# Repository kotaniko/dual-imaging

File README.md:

# Dual-Imaging Display
This prototype is developed in partial fulfillment for a Master's degree to prove that fiber-optic interconnection is a suitable high-speed interconnection for CubeSat platforms. The thesis is available [here](https://gatech.edu).

## Introduction
This repository contains the development details of dual-imaging display using the BF4M fiber-optic module with FPGAs and Raspberry Pi Compute Module 4. The goal of this prototype is to demonstrate the high-speed interconnection using a fiber-optic transceiver for CubeSat platforms.

## Hardware
* Artix-7 FPGA module from Trenz Electronic: [TE0714-03-50-2IAC6](https://shop.trenz-electronic.de/en/TE0714-03-50-2IAC6-FPGA-Module-with-Xilinx-Artix-7-XC7A50T-2CSG325I-1.8V-Configuration-4-x-3-cm)

* [Raspberry Pi Compute Module 4](https://www.raspberrypi.com/products/compute-module-4)

* [BF4M](https://www.hirose.com/product/series/BF4M) fiber-optic module from Hirose Electronic

* [Pcam 5C](https://digilent.com/shop/pcam-5c-5-mp-fixed-focus-color-camera-module) camera module from Digilent

## System Architecture
Below shows the overview of the dual-imaging display system.

MIPI CSI-2 Rx Subsystem IP core is used for interfacing with the camera modules, and Aurora8B10B Ip core for interfacing with the fiber-optic transceiver operating up to 6.25 Gbps. On the receiver FPGA, DMA/Bridge Subsystem for PCI Express IP core is used for interfacing with the Raspberry Pi Compute Module 4 over PCIe.

Post-synthesis re-routing on the RX FPGA is needed for GTP clock signals as Aurora8B10B and PCIe core require different clock source. The details are explained in **Vivado/README.md**.

## Images of the Prototype

## Demonstration Video
Below video demonstrates that the two camera data stream are transmitted to the Raspberry Pi Compute Module 4 at 1.0 Gbps. The RPiCM4 was capable of receiving the data stream to /dev/null at 2.0 Gbps, but the maximum data rate to write the data stream to its RAM was 1.0 Gbps.

https://user-images.githubusercontent.com/22487346/164984304-3e48e70a-c83b-4c12-9497-3e3b185fa539.mov

The validation method discussed in the thesis demonstrated that the BF4M fiber-optic module achieved the maximum data rate of 6.25 Gbps at the power consumption of 90 mW.

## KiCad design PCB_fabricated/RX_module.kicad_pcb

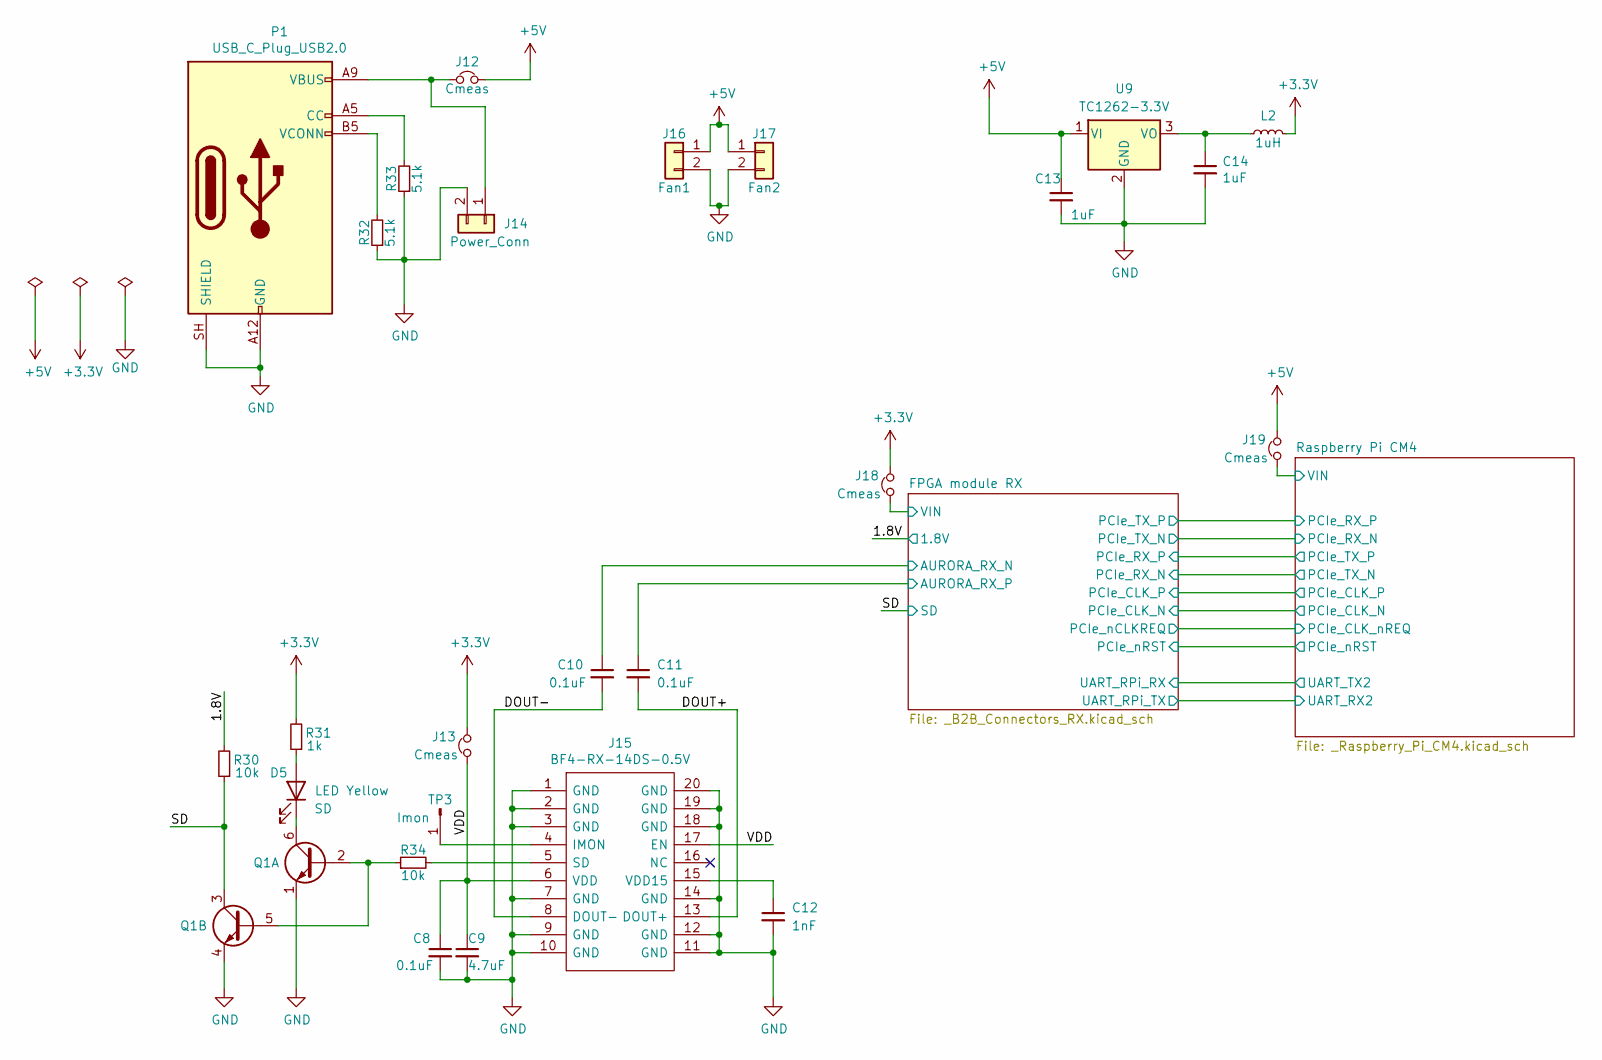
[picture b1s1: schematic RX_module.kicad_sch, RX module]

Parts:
C8, C10, C11: 0.1uF; C_0603_1608Metric_Pad1.08x0.95mm_HandSolder
C9: 4.7uF; C_0603_1608Metric_Pad1.08x0.95mm_HandSolder
C12: 1nF; C_0603_1608Metric_Pad1.08x0.95mm_HandSolder
C13, C14: 1uF; C_0603_1608Metric_Pad1.08x0.95mm_HandSolder
D5: LED Yellow; LED_0603_1608Metric_Pad1.05x0.95mm_HandSolder
J12, J13, J18, J19: Cmeas; PinHeader_1x02_P2.54mm_Vertical
J14: Power_Conn; JST_XH_B2B-XH-A_1x02_P2.50mm_Vertical
J15: BF4-RX-14DS-0.5V; BF4RX14DS05V
J16: Fan1; PinHeader_1x02_P2.54mm_Vertical
J17: Fan2; PinHeader_1x02_P2.54mm_Vertical
L2: 1uH; L_0603_1608Metric_Pad1.05x0.95mm_HandSolder
P1: USB_C_Plug_USB2.0; USB4125-GF-A
Q1: BC847BS; SOT-363_SC-70-6_Handsoldering
R30, R34: 10k; R_0603_1608Metric_Pad0.98x0.95mm_HandSolder
R31: 1k; R_0603_1608Metric_Pad0.98x0.95mm_HandSolder
R32, R33: 5.1k; R_0603_1608Metric_Pad0.98x0.95mm_HandSolder
TP3: Imon; TestPoint_Loop_D2.50mm_Drill1.0mm
U9: TC1262-3.3V; SOT-223-3_TabPin2

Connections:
+3V3: J13.2, J18.2, L2.2, R31.2
+5V: C13.1, J12.2, J16.1, J17.1, J19.2, U9.1 (VI)
/1.8V: R30.2; also elsewhere on the board
/DOUT+: C11.2, J15.13 (DOUT+)
/DOUT-: C10.2, J15.8 (DOUT-)
/FPGA module RX/AURORA_RX_N: C10.1; also elsewhere on the board
/FPGA module RX/AURORA_RX_P: C11.1; also elsewhere on the board
/FPGA module RX/VIN: J18.1; also elsewhere on the board
/Raspberry Pi CM4/VIN: J19.1; also elsewhere on the board
/SD: Q1.3 (C2), R30.1; also elsewhere on the board
/VDD: C8.1, C9.1, J13.1, J15.6 (VDD), J15.17 (EN)
GND: C8.2, C9.2, C12.2, C13.2, C14.2, J14.2, J15.1 (GND), J15.2 (GND), J15.3 (GND), J15.7 (GND), J15.9 (GND), J15.10 (GND), J15.11 (GND), J15.12 (GND), J15.14 (GND), J15.18 (GND), J15.19 (GND), J15.20 (GND), J16.2, J17.2, P1.A12 (GND), P1.B12 (GND), P1.SH (SHIELD), Q1.1 (E1), Q1.4 (E2), R32.1, R33.1, U9.2 (GND); also elsewhere on the board
unnamed: C12.1, J15.15 (VDD15)
unnamed: C14.1, L2.1, U9.3 (VO)
unnamed: D5.1 (K), Q1.6 (C1)
unnamed: D5.2 (A), R31.1
unnamed: J12.1, J14.1, P1.A9 (VBUS)
unnamed: J15.4 (IMON), TP3.1
unnamed: J15.5 (SD), R34.2
unnamed: P1.A5 (CC), R33.2
unnamed: P1.B5 (VCONN), R32.2
unnamed: Q1.2 (B1), Q1.5 (B2), R34.1

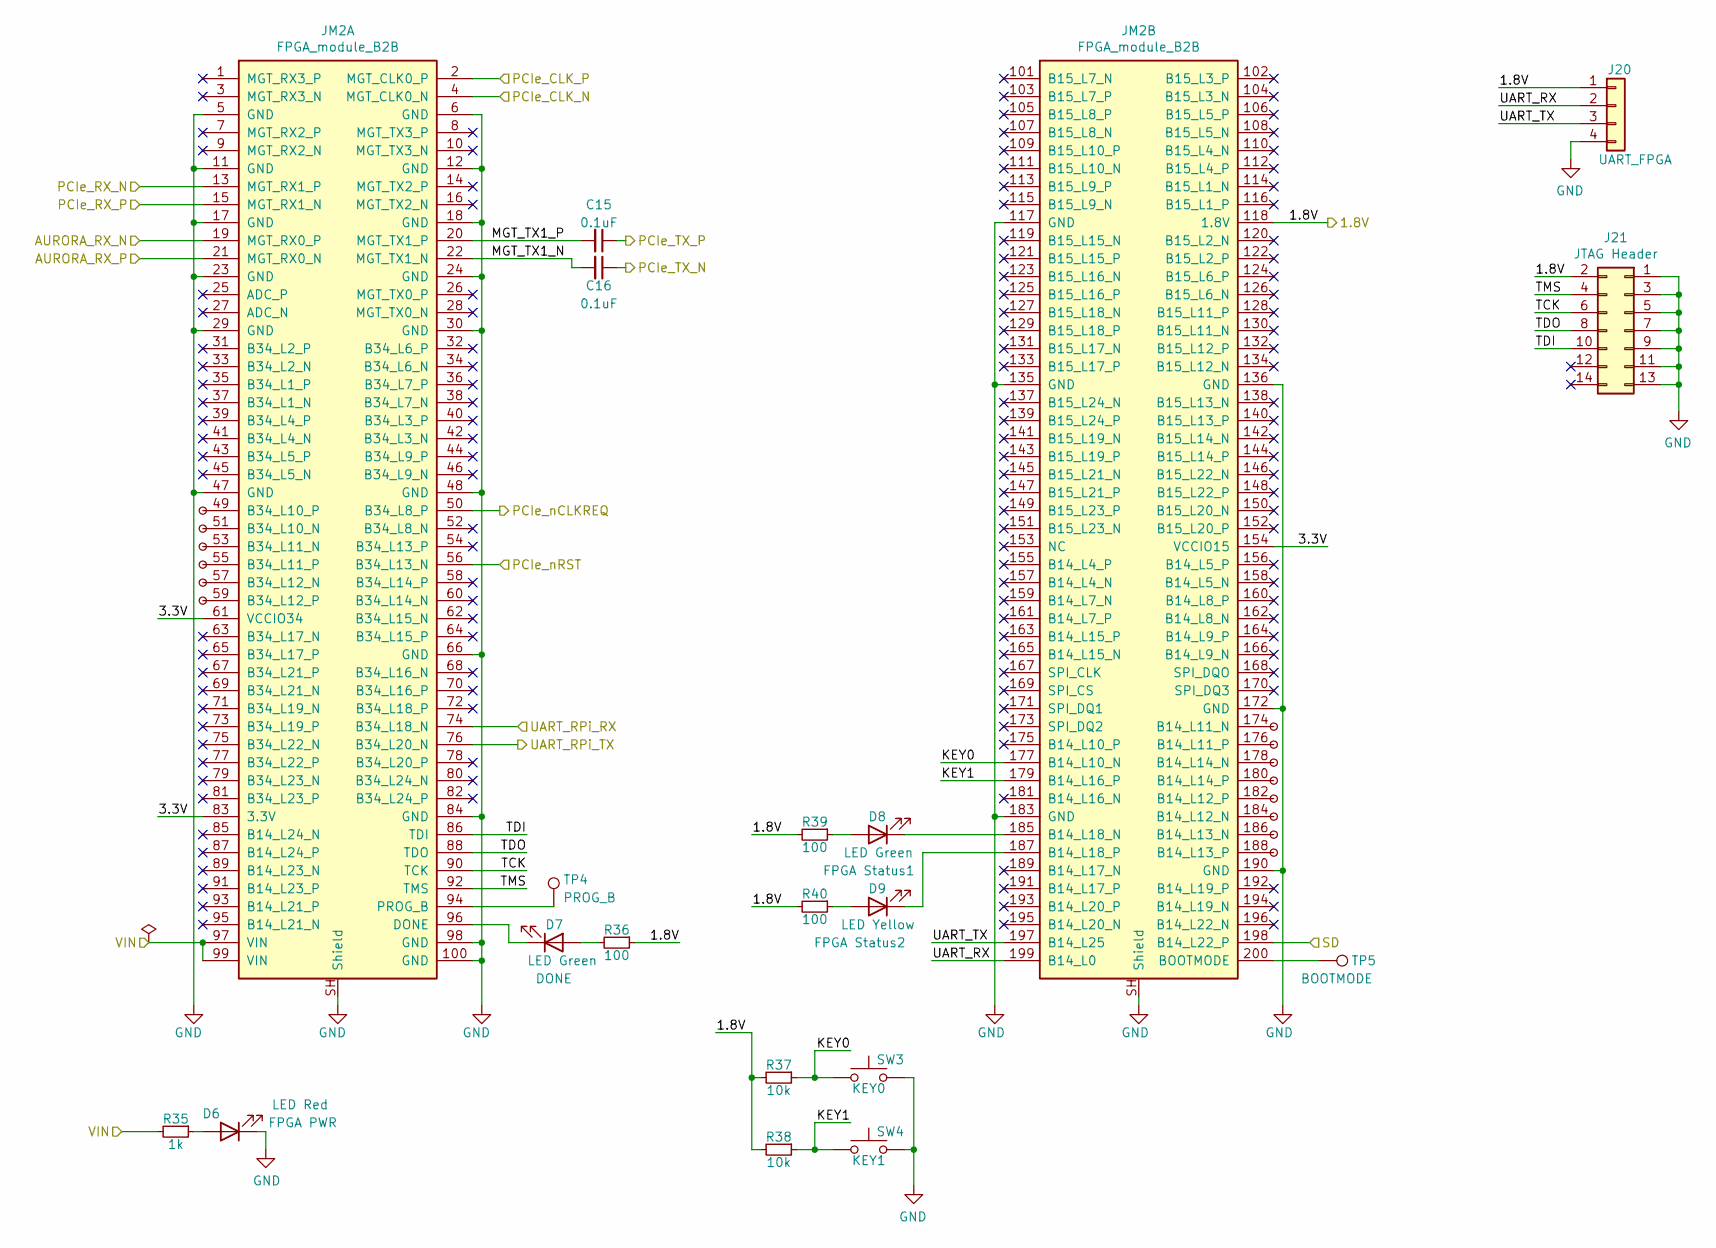
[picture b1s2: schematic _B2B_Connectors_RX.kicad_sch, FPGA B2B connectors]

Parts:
C15, C16: 0.1uF; C_0603_1608Metric_Pad1.08x0.95mm_HandSolder
D6: LED Red; LED_0603_1608Metric_Pad1.05x0.95mm_HandSolder
D7, D8: LED Green; LED_0603_1608Metric_Pad1.05x0.95mm_HandSolder
D9: LED Yellow; LED_0603_1608Metric_Pad1.05x0.95mm_HandSolder
J20: UART_FPGA; PinHeader_1x04_P2.54mm_Vertical
J21: JTAG Header; JTAG_Header
JM2: FPGA_module_B2B
P2, P3, P4, P5, P6, P7, P8, P9, P10, P11, P12, P13, P14, P15: ExtPad; ExtPoint_Pad_1.0x2.0mm
R35: 1k; R_0603_1608Metric_Pad0.98x0.95mm_HandSolder
R36, R39, R40: 100; R_0603_1608Metric_Pad0.98x0.95mm_HandSolder
R37, R38: 10k; R_0603_1608Metric_Pad0.98x0.95mm_HandSolder
SW3: KEY0; SW_SPST_PTS636
SW4: KEY1; SW_SPST_PTS636
TP4: PROG_B; TestPoint_Loop_D2.50mm_Drill1.0mm
TP5: BOOTMODE; TestPoint_Loop_D2.50mm_Drill1.0mm

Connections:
/1.8V: J20.1, J21.2, JM2.118 (1.8V), R36.1, R37.2, R38.2, R39.2, R40.2; also elsewhere on the board
/FPGA module RX/3.3V: JM2.61 (VCCIO34), JM2.83 (3.3V), JM2.154 (VCCIO15)
/FPGA module RX/AURORA_RX_N: JM2.19 (MGT_RX0_P); also elsewhere on the board
/FPGA module RX/AURORA_RX_P: JM2.21 (MGT_RX0_N); also elsewhere on the board
/FPGA module RX/KEY0: JM2.177 (B14_L10_N), R37.1, SW3.2
/FPGA module RX/KEY1: JM2.179 (B14_L16_P), R38.1, SW4.2
/FPGA module RX/MGT_TX1_N: C16.2, JM2.22 (MGT_TX1_N)
/FPGA module RX/MGT_TX1_P: C15.2, JM2.20 (MGT_TX1_P)
/FPGA module RX/PCIe_CLK_N: JM2.4 (MGT_CLK0_N); also elsewhere on the board
/FPGA module RX/PCIe_CLK_P: JM2.2 (MGT_CLK0_P); also elsewhere on the board
/FPGA module RX/PCIe_RX_N: JM2.13 (MGT_RX1_P); also elsewhere on the board
/FPGA module RX/PCIe_RX_P: JM2.15 (MGT_RX1_N); also elsewhere on the board
/FPGA module RX/PCIe_nRST: JM2.56 (B34_L13_N); also elsewhere on the board
/FPGA module RX/TCK: J21.6, JM2.90 (TCK)
/FPGA module RX/TDI: J21.10, JM2.86 (TDI)
/FPGA module RX/TDO: J21.8, JM2.88 (TDO)
/FPGA module RX/TMS: J21.4, JM2.92 (TMS)
/FPGA module RX/UART_RPi_RX: JM2.74 (B34_L18_N); also elsewhere on the board
/FPGA module RX/UART_RPi_TX: JM2.76 (B34_L20_N); also elsewhere on the board
/FPGA module RX/UART_RX: J20.2, JM2.199 (B14_L0)
/FPGA module RX/UART_TX: J20.3, JM2.197 (B14_L25)
/FPGA module RX/VIN: JM2.97 (VIN), JM2.99 (VIN), R35.2; also elsewhere on the board
/Raspberry Pi CM4/PCIe_CLK_nREQ: JM2.50 (B34_L8_P); also elsewhere on the board
/Raspberry Pi CM4/PCIe_RX_N: C16.1; also elsewhere on the board
/Raspberry Pi CM4/PCIe_RX_P: C15.1; also elsewhere on the board
/SD: JM2.198 (B14_L22_P); also elsewhere on the board
GND: D6.1 (K), J20.4, J21.1, J21.3, J21.5, J21.7, J21.9, J21.11, J21.13, JM2.5 (GND), JM2.6 (GND), JM2.11 (GND), JM2.12 (GND), JM2.17 (GND), JM2.18 (GND), JM2.23 (GND), JM2.24 (GND), JM2.29 (GND), JM2.30 (GND), JM2.47 (GND), JM2.48 (GND), JM2.66 (GND), JM2.84 (GND), JM2.98 (GND), JM2.100 (GND), JM2.117 (GND), JM2.135 (GND), JM2.136 (GND), JM2.172 (GND), JM2.183 (GND), JM2.190 (GND), JM2.SH (Shield), SW3.1, SW4.1; also elsewhere on the board
unnamed: D6.2 (A), R35.1
unnamed: D7.1 (K), JM2.96 (DONE)
unnamed: D7.2 (A), R36.2
unnamed: D8.1 (K), JM2.185 (B14_L18_N)
unnamed: D8.2 (A), R39.1
unnamed: D9.1 (K), JM2.187 (B14_L18_P)
unnamed: D9.2 (A), R40.1
unnamed: JM2.49 (B34_L10_P), P2.1
unnamed: JM2.51 (B34_L10_N), P3.1
unnamed: JM2.53 (B34_L11_N), P4.1
unnamed: JM2.55 (B34_L11_P), P5.1
unnamed: JM2.57 (B34_L12_N), P6.1
unnamed: JM2.59 (B34_L12_P), P7.1
unnamed: JM2.94 (PROG_B), TP4.1
unnamed: JM2.174 (B14_L11_N), P8.1
unnamed: JM2.176 (B14_L11_P), P9.1
unnamed: JM2.178 (B14_L14_N), P10.1
unnamed: JM2.180 (B14_L14_P), P11.1
unnamed: JM2.182 (B14_L12_P), P12.1
unnamed: JM2.184 (B14_L12_N), P13.1
unnamed: JM2.186 (B14_L13_N), P14.1
unnamed: JM2.188 (B14_L13_P), P15.1
unnamed: JM2.200 (BOOTMODE), TP5.1

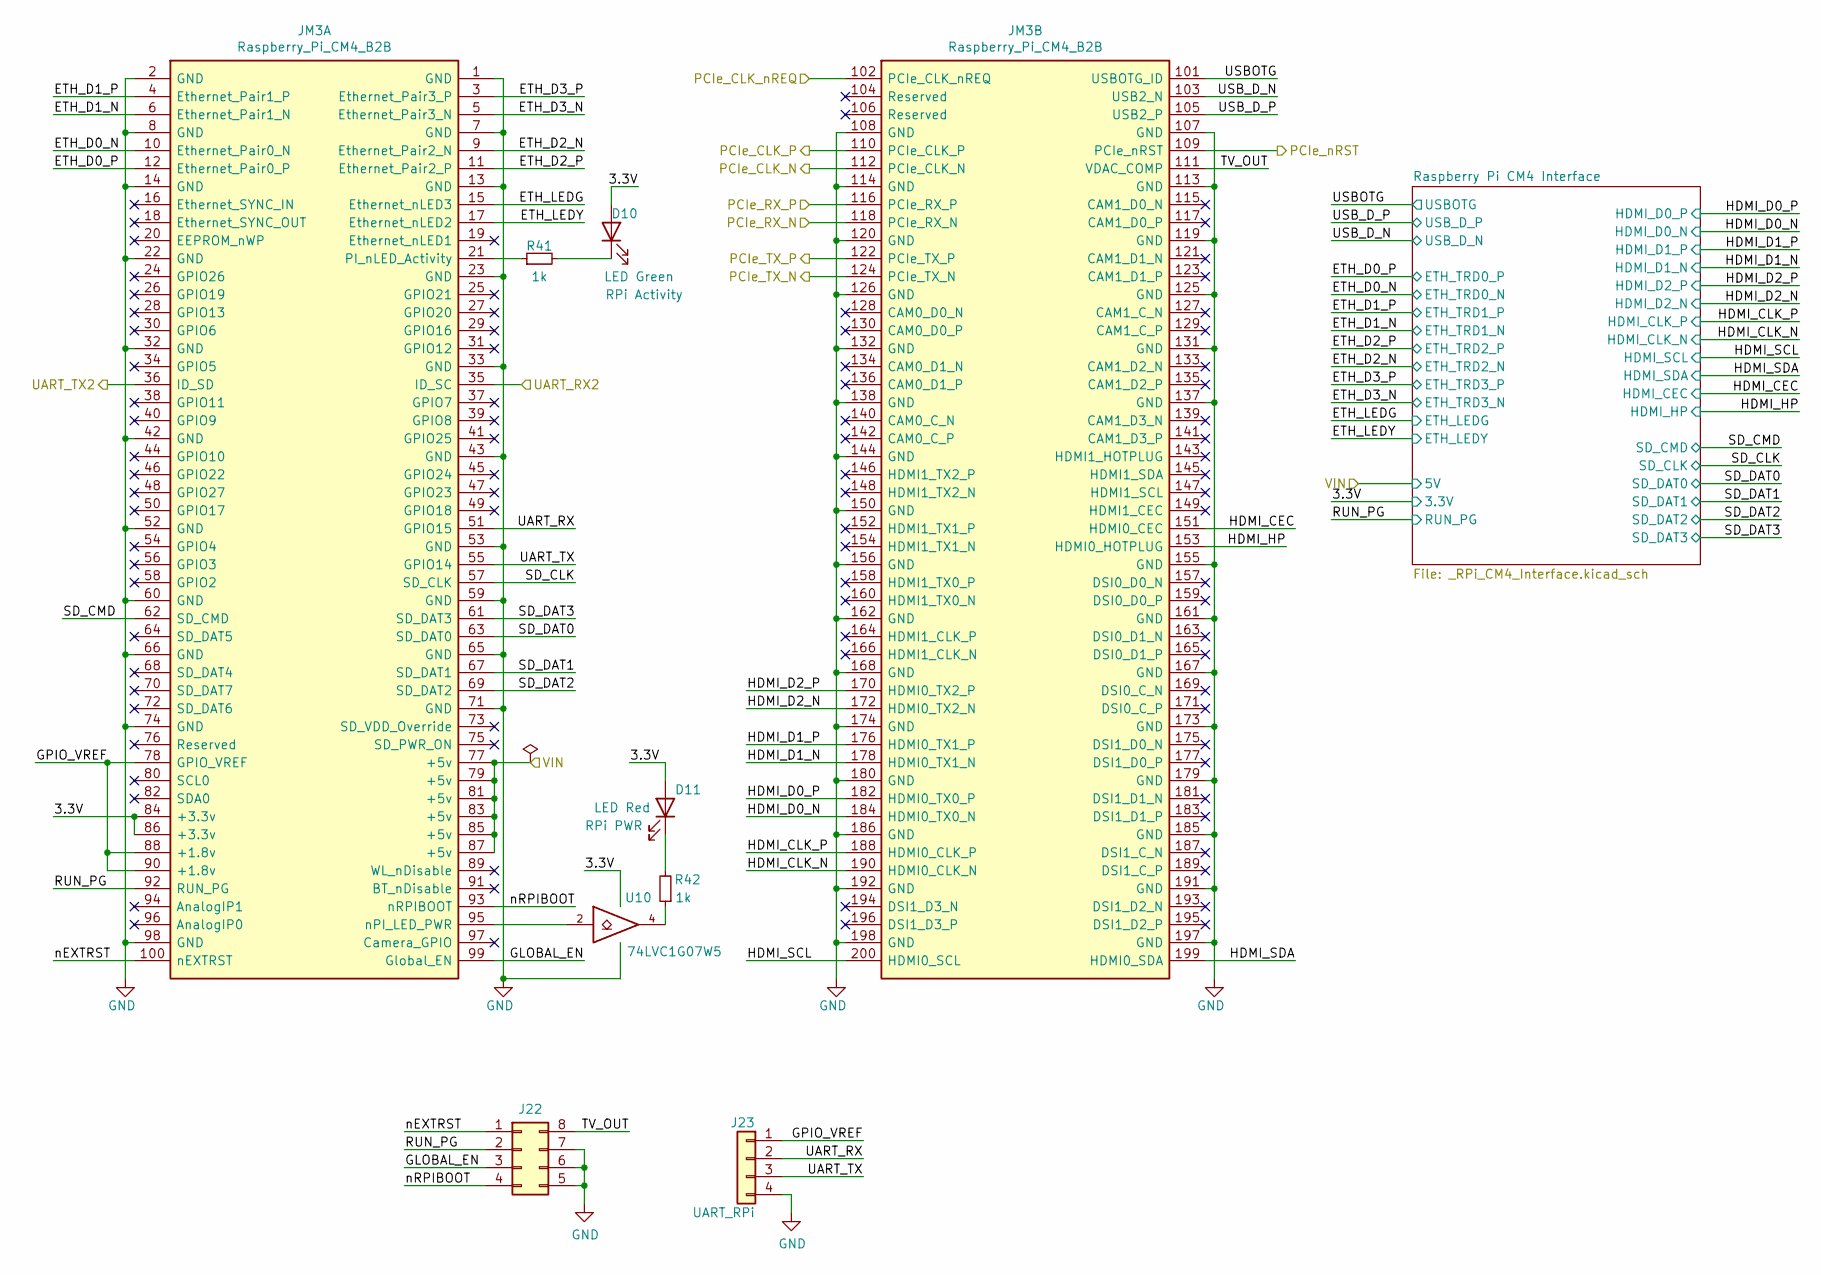
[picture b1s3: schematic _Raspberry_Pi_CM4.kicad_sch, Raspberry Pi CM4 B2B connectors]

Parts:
D10: LED Green; LED_0603_1608Metric_Pad1.05x0.95mm_HandSolder
D11: LED Red; LED_0603_1608Metric_Pad1.05x0.95mm_HandSolder
J22: RPi_CONFIG; PinHeader_2x04_P2.54mm_Vertical
J23: UART_RPi; PinHeader_1x04_P2.54mm_Vertical
JM3: Raspberry_Pi_CM4_B2B; Raspberry_Pi_Compute_Module_4
R41, R42: 1k; R_0603_1608Metric_Pad0.98x0.95mm_HandSolder
U10: 74LVC1G07W5; SOT-23-5_HandSoldering

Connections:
/FPGA module RX/PCIe_CLK_N: JM3.112 (PCIe_CLK_N); also elsewhere on the board
/FPGA module RX/PCIe_CLK_P: JM3.110 (PCIe_CLK_P); also elsewhere on the board
/FPGA module RX/PCIe_RX_N: JM3.124 (PCIe_TX_N); also elsewhere on the board
/FPGA module RX/PCIe_RX_P: JM3.122 (PCIe_TX_P); also elsewhere on the board
/FPGA module RX/PCIe_nRST: JM3.109 (PCIe_nRST); also elsewhere on the board
/FPGA module RX/UART_RPi_RX: JM3.36 (ID_SD); also elsewhere on the board
/FPGA module RX/UART_RPi_TX: JM3.35 (ID_SC); also elsewhere on the board
/Raspberry Pi CM4/ETH_D0_N: JM3.10 (Ethernet_Pair0_N); also elsewhere on the board
/Raspberry Pi CM4/ETH_D0_P: JM3.12 (Ethernet_Pair0_P); also elsewhere on the board
/Raspberry Pi CM4/ETH_D1_N: JM3.6 (Ethernet_Pair1_N); also elsewhere on the board
/Raspberry Pi CM4/ETH_D1_P: JM3.4 (Ethernet_Pair1_P); also elsewhere on the board
/Raspberry Pi CM4/ETH_D2_N: JM3.9 (Ethernet_Pair2_N); also elsewhere on the board
/Raspberry Pi CM4/ETH_D2_P: JM3.11 (Ethernet_Pair2_P); also elsewhere on the board
/Raspberry Pi CM4/ETH_D3_N: JM3.5 (Ethernet_Pair3_N); also elsewhere on the board
/Raspberry Pi CM4/ETH_D3_P: JM3.3 (Ethernet_Pair3_P); also elsewhere on the board
/Raspberry Pi CM4/ETH_LEDG: JM3.15 (Ethernet_nLED3); also elsewhere on the board
/Raspberry Pi CM4/ETH_LEDY: JM3.17 (Ethernet_nLED2); also elsewhere on the board
/Raspberry Pi CM4/GLOBAL_EN: J22.3, JM3.99 (Global_EN)
/Raspberry Pi CM4/GPIO_VREF: J23.1, JM3.78 (GPIO_VREF), JM3.88 (+1.8v), JM3.90 (+1.8v)
/Raspberry Pi CM4/HDMI_CEC: JM3.151 (HDMI0_CEC); also elsewhere on the board
/Raspberry Pi CM4/HDMI_CLK_N: JM3.190 (HDMI0_CLK_N); also elsewhere on the board
/Raspberry Pi CM4/HDMI_CLK_P: JM3.188 (HDMI0_CLK_P); also elsewhere on the board
/Raspberry Pi CM4/HDMI_D0_N: JM3.184 (HDMI0_TX0_N); also elsewhere on the board
/Raspberry Pi CM4/HDMI_D0_P: JM3.182 (HDMI0_TX0_P); also elsewhere on the board
/Raspberry Pi CM4/HDMI_D1_N: JM3.178 (HDMI0_TX1_N); also elsewhere on the board
/Raspberry Pi CM4/HDMI_D1_P: JM3.176 (HDMI0_TX1_P); also elsewhere on the board
/Raspberry Pi CM4/HDMI_D2_N: JM3.172 (HDMI0_TX2_N); also elsewhere on the board
/Raspberry Pi CM4/HDMI_D2_P: JM3.170 (HDMI0_TX2_P); also elsewhere on the board
/Raspberry Pi CM4/HDMI_HP: JM3.153 (HDMI0_HOTPLUG); also elsewhere on the board
/Raspberry Pi CM4/HDMI_SCL: JM3.200 (HDMI0_SCL); also elsewhere on the board
/Raspberry Pi CM4/HDMI_SDA: JM3.199 (HDMI0_SDA); also elsewhere on the board
/Raspberry Pi CM4/PCIe_CLK_nREQ: JM3.102 (PCIe_CLK_nREQ); also elsewhere on the board
/Raspberry Pi CM4/PCIe_RX_N: JM3.118 (PCIe_RX_N); also elsewhere on the board
/Raspberry Pi CM4/PCIe_RX_P: JM3.116 (PCIe_RX_P); also elsewhere on the board
/Raspberry Pi CM4/RUN_PG: J22.2, JM3.92 (RUN_PG); also elsewhere on the board
/Raspberry Pi CM4/SD_CLK: JM3.57 (SD_CLK); also elsewhere on the board
/Raspberry Pi CM4/SD_CMD: JM3.62 (SD_CMD); also elsewhere on the board
/Raspberry Pi CM4/SD_DAT0: JM3.63 (SD_DAT0); also elsewhere on the board
/Raspberry Pi CM4/SD_DAT1: JM3.67 (SD_DAT1); also elsewhere on the board
/Raspberry Pi CM4/SD_DAT2: JM3.69 (SD_DAT2); also elsewhere on the board
/Raspberry Pi CM4/SD_DAT3: JM3.61 (SD_DAT3); also elsewhere on the board
/Raspberry Pi CM4/TV_OUT: J22.8, JM3.111 (VDAC_COMP)
/Raspberry Pi CM4/UART_RX: J23.2, JM3.51 (GPIO15)
/Raspberry Pi CM4/UART_TX: J23.3, JM3.55 (GPIO14)
/Raspberry Pi CM4/USBOTG: JM3.101 (USBOTG_ID); also elsewhere on the board
/Raspberry Pi CM4/USB_D_N: JM3.103 (USB2_N); also elsewhere on the board
/Raspberry Pi CM4/USB_D_P: JM3.105 (USB2_P); also elsewhere on the board
/Raspberry Pi CM4/VIN: JM3.77 (+5v), JM3.79 (+5v), JM3.81 (+5v), JM3.83 (+5v), JM3.85 (+5v), JM3.87 (+5v); also elsewhere on the board
/Raspberry Pi CM4/nEXTRST: J22.1, JM3.100 (nEXTRST)
/Raspberry Pi CM4/nRPIBOOT: J22.4, JM3.93 (nRPIBOOT)
GND: J22.5, J22.6, J22.7, J23.4, JM3.1 (GND), JM3.2 (GND), JM3.7 (GND), JM3.8 (GND), JM3.13 (GND), JM3.14 (GND), JM3.22 (GND), JM3.23 (GND), JM3.32 (GND), JM3.33 (GND), JM3.42 (GND), JM3.43 (GND), JM3.52 (GND), JM3.53 (GND), JM3.59 (GND), JM3.60 (GND), JM3.65 (GND), JM3.66 (GND), JM3.71 (GND), JM3.74 (GND), JM3.98 (GND), JM3.107 (GND), JM3.108 (GND), JM3.113 (GND), JM3.114 (GND), JM3.119 (GND), JM3.120 (GND), JM3.125 (GND), JM3.126 (GND), JM3.131 (GND), JM3.132 (GND), JM3.137 (GND), JM3.138 (GND), JM3.144 (GND), JM3.150 (GND), JM3.155 (GND), JM3.156 (GND), JM3.161 (GND), JM3.162 (GND), JM3.167 (GND), JM3.168 (GND), JM3.173 (GND), JM3.174 (GND), JM3.179 (GND), JM3.180 (GND), JM3.185 (GND), JM3.186 (GND), JM3.191 (GND), JM3.192 (GND), JM3.197 (GND), JM3.198 (GND), U10.3 (GND); also elsewhere on the board
unnamed: D10.1 (K), R41.2
unnamed: D11.1 (K), R42.2
unnamed: JM3.21 (PI_nLED_Activity), R41.1
unnamed: JM3.95 (nPI_LED_PWR), U10.2
unnamed: R42.1, U10.4
VCC: D10.2 (A), D11.2 (A), JM3.84 (+3.3v), JM3.86 (+3.3v), U10.5 (VCC); also elsewhere on the board

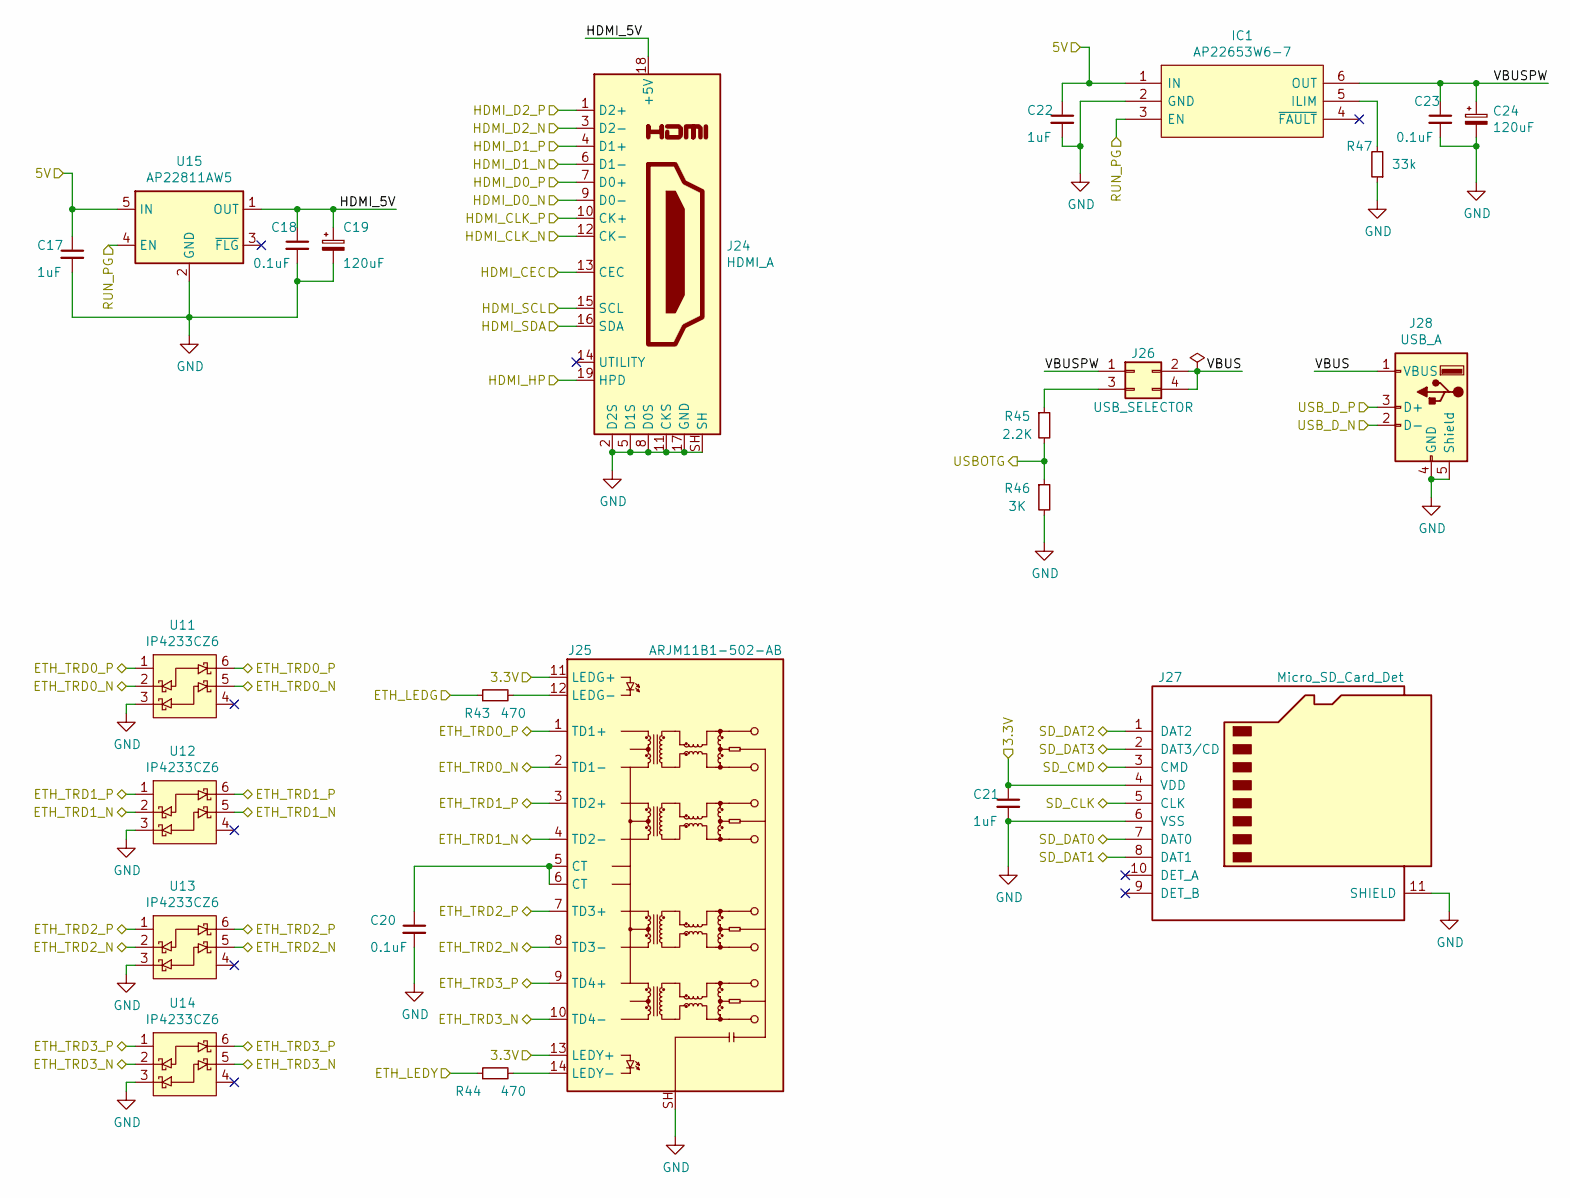
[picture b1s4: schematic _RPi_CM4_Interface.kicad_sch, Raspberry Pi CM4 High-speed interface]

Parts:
C17, C21, C22: 1uF; C_0603_1608Metric_Pad1.08x0.95mm_HandSolder
C18, C20, C23: 0.1uF; C_0603_1608Metric_Pad1.08x0.95mm_HandSolder
C19, C24: 120uF; CP_Radial_D6.3mm_P2.50mm
IC1: AP22653W6-7; SOT-23-6_Handsoldering
J24: HDMI_A; SS-53000-001
J25: ARJM11B1-502-AB; ARJM11B1-502-AB-ER2
J26: USB_SELECTOR; PinHeader_2x02_P2.54mm_Vertical
J27: Micro_SD_Card_Det; Molex_1051620001
J28: USB_A; USB_A_Stewart_SS-52100-001_Horizontal
R43, R44: 470; R_0603_1608Metric_Pad0.98x0.95mm_HandSolder
R45: 2.2K; R_0603_1608Metric_Pad0.98x0.95mm_HandSolder
R46: 3K; R_0603_1608Metric_Pad0.98x0.95mm_HandSolder
R47: 33k; R_0603_1608Metric_Pad0.98x0.95mm_HandSolder
U11, U12, U13, U14: IP4233CZ6; SOT-363_SC-70-6_Handsoldering
U15: AP22811AW5; SOT-23-5_HandSoldering

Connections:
/Raspberry Pi CM4/ETH_D0_N: J25.2 (TD1-), U11.2 (C1), U11.5 (C2); also elsewhere on the board
/Raspberry Pi CM4/ETH_D0_P: J25.1 (TD1+), U11.1, U11.6 (C1); also elsewhere on the board
/Raspberry Pi CM4/ETH_D1_N: J25.4 (TD2-), U12.2 (C1), U12.5 (C2); also elsewhere on the board
/Raspberry Pi CM4/ETH_D1_P: J25.3 (TD2+), U12.1, U12.6 (C1); also elsewhere on the board
/Raspberry Pi CM4/ETH_D2_N: J25.8 (TD3-), U13.2 (C1), U13.5 (C2); also elsewhere on the board
/Raspberry Pi CM4/ETH_D2_P: J25.7 (TD3+), U13.1, U13.6 (C1); also elsewhere on the board
/Raspberry Pi CM4/ETH_D3_N: J25.10 (TD4-), U14.2 (C1), U14.5 (C2); also elsewhere on the board
/Raspberry Pi CM4/ETH_D3_P: J25.9 (TD4+), U14.1, U14.6 (C1); also elsewhere on the board
/Raspberry Pi CM4/ETH_LEDG: R43.1; also elsewhere on the board
/Raspberry Pi CM4/ETH_LEDY: R44.1; also elsewhere on the board
/Raspberry Pi CM4/HDMI_CEC: J24.13 (CEC); also elsewhere on the board
/Raspberry Pi CM4/HDMI_CLK_N: J24.12 (CK-); also elsewhere on the board
/Raspberry Pi CM4/HDMI_CLK_P: J24.10 (CK+); also elsewhere on the board
/Raspberry Pi CM4/HDMI_D0_N: J24.9 (D0-); also elsewhere on the board
/Raspberry Pi CM4/HDMI_D0_P: J24.7 (D0+); also elsewhere on the board
/Raspberry Pi CM4/HDMI_D1_N: J24.6 (D1-); also elsewhere on the board
/Raspberry Pi CM4/HDMI_D1_P: J24.4 (D1+); also elsewhere on the board
/Raspberry Pi CM4/HDMI_D2_N: J24.3 (D2-); also elsewhere on the board
/Raspberry Pi CM4/HDMI_D2_P: J24.1 (D2+); also elsewhere on the board
/Raspberry Pi CM4/HDMI_HP: J24.19 (HPD); also elsewhere on the board
/Raspberry Pi CM4/HDMI_SCL: J24.15 (SCL); also elsewhere on the board
/Raspberry Pi CM4/HDMI_SDA: J24.16 (SDA); also elsewhere on the board
/Raspberry Pi CM4/RUN_PG: IC1.3 (EN), U15.4 (EN); also elsewhere on the board
/Raspberry Pi CM4/Raspberry Pi CM4 Interface/HDMI_5V: C18.1, C19.1, J24.18 (+5V), U15.1 (OUT)
/Raspberry Pi CM4/Raspberry Pi CM4 Interface/VBUS: J26.2, J26.4, J28.1 (VBUS)
/Raspberry Pi CM4/Raspberry Pi CM4 Interface/VBUSPW: C23.1, C24.1, IC1.6 (OUT), J26.1
/Raspberry Pi CM4/SD_CLK: J27.5 (CLK); also elsewhere on the board
/Raspberry Pi CM4/SD_CMD: J27.3 (CMD); also elsewhere on the board
/Raspberry Pi CM4/SD_DAT0: J27.7 (DAT0); also elsewhere on the board
/Raspberry Pi CM4/SD_DAT1: J27.8 (DAT1); also elsewhere on the board
/Raspberry Pi CM4/SD_DAT2: J27.1 (DAT2); also elsewhere on the board
/Raspberry Pi CM4/SD_DAT3: J27.2 (DAT3/CD); also elsewhere on the board
/Raspberry Pi CM4/USBOTG: R45.2, R46.1; also elsewhere on the board
/Raspberry Pi CM4/USB_D_N: J28.2 (D-); also elsewhere on the board
/Raspberry Pi CM4/USB_D_P: J28.3 (D+); also elsewhere on the board
/Raspberry Pi CM4/VIN: C17.1, C22.1, IC1.1 (IN), U15.5 (IN); also elsewhere on the board
GND: C17.2, C18.2, C19.2, C20.2, C21.2, C22.2, C23.2, C24.2, IC1.2 (GND), J24.2 (D2S), J24.5 (D1S), J24.8 (D0S), J24.11 (CKS), J24.17 (GND), J24.SH, J25.SH, J27.6 (VSS), J27.11 (SHIELD), J28.4 (GND), J28.5 (Shield), R46.2, R47.1, U11.3 (C2), U12.3 (C2), U13.3 (C2), U14.3 (C2), U15.2 (GND); also elsewhere on the board
unnamed: C20.1, J25.5 (CT), J25.6 (CT)
unnamed: IC1.5 (ILIM), R47.2
unnamed: J25.12 (LEDG-), R43.2
unnamed: J25.14 (LEDY-), R44.2
unnamed: J26.3, R45.1
VCC: C21.1, J25.11 (LEDG+), J25.13 (LEDY+), J27.4 (VDD); also elsewhere on the board

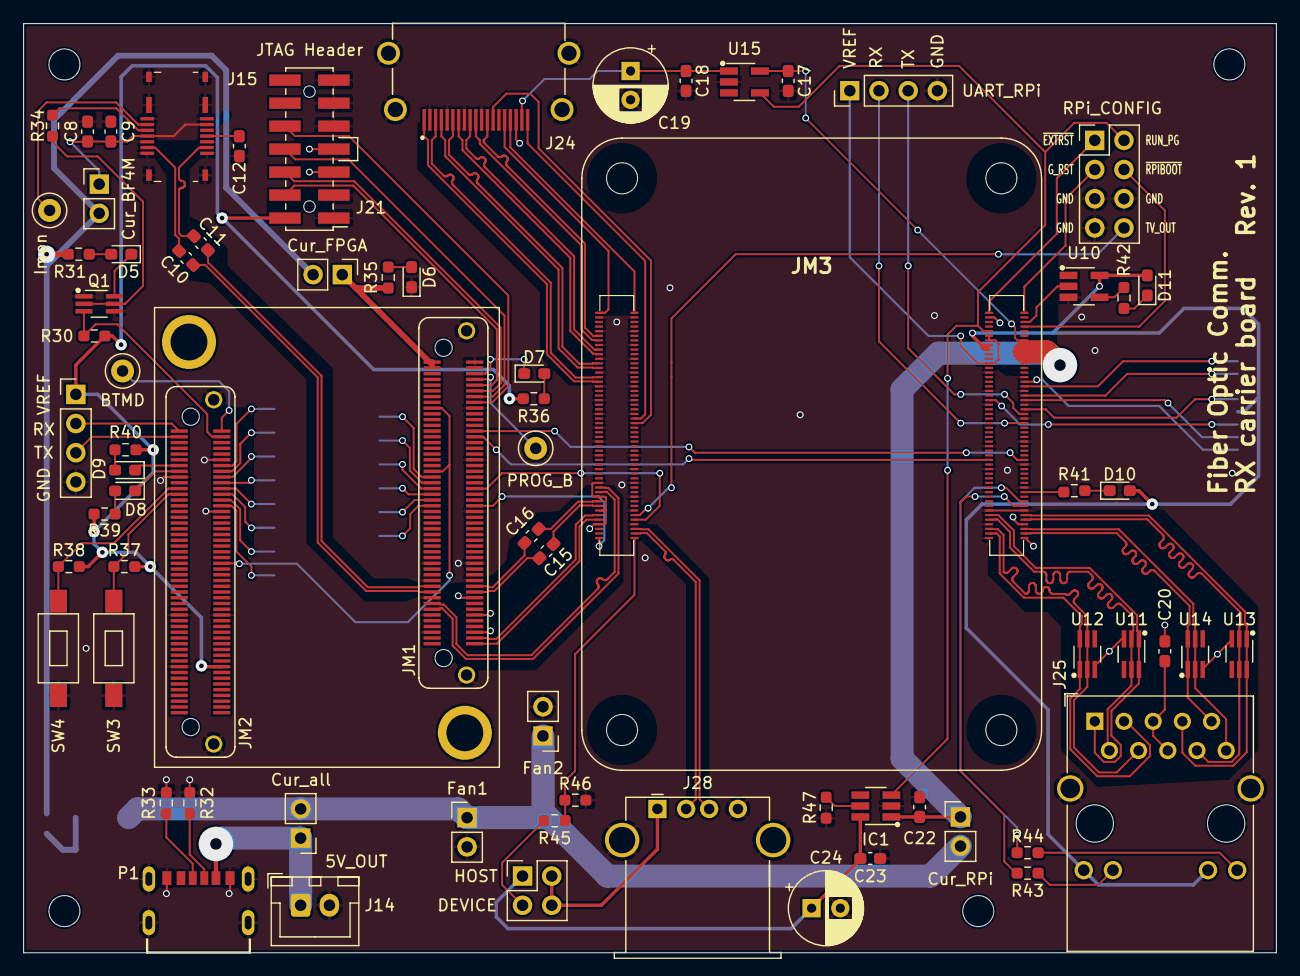
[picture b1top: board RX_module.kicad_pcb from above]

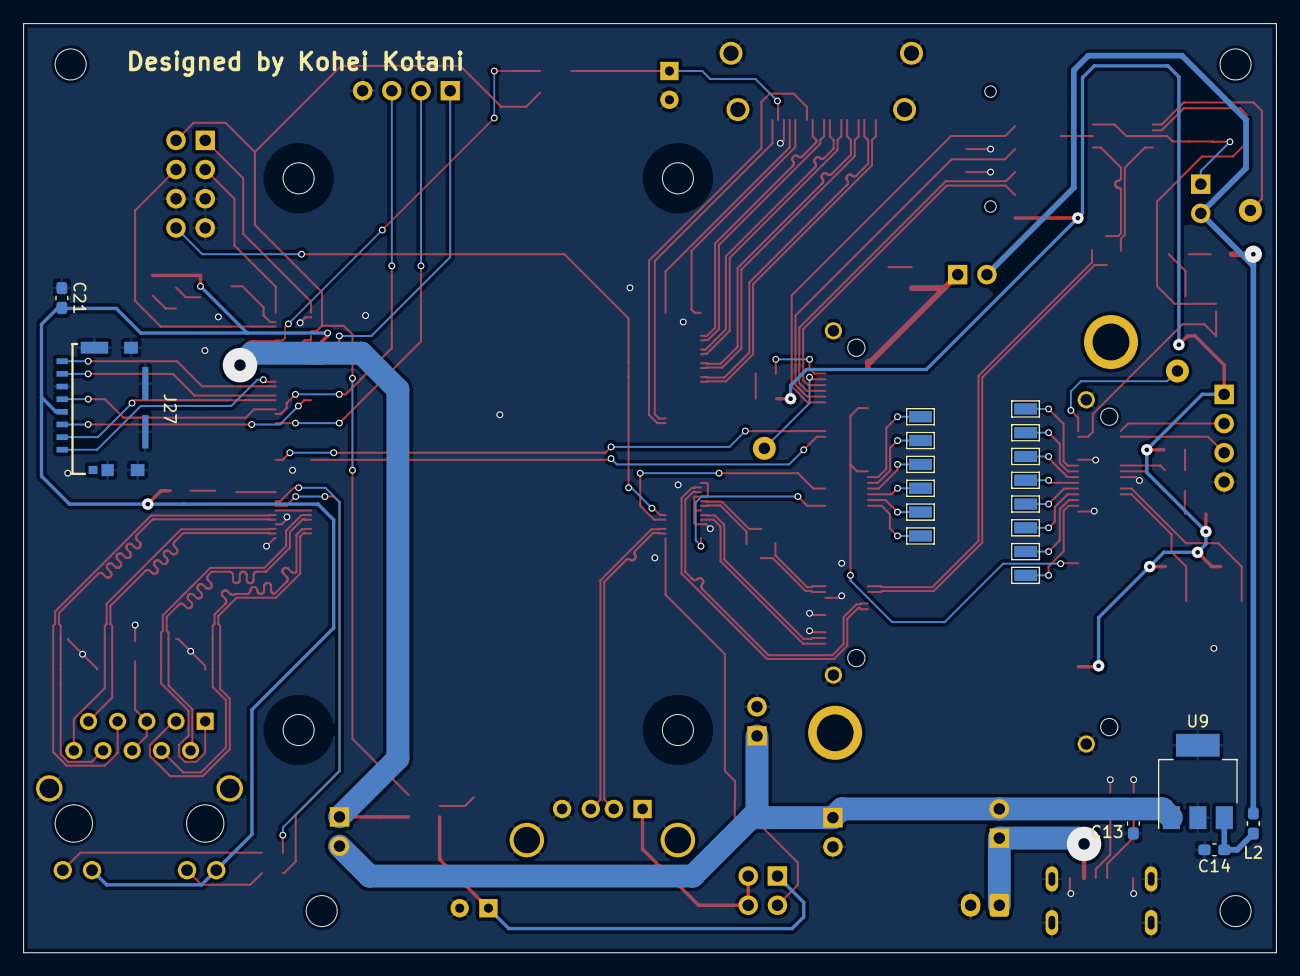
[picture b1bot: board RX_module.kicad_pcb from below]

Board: 2 copper layers, 109.0 x 80.8 mm, 91 parts (20 on the bottom side), 119 nets.
